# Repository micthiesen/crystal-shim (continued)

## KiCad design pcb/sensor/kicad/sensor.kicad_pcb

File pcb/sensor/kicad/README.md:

# Sensor routing handoff

Open [sensor.kicad_pro](sensor.kicad_pro). The compact sensor is **18 × 64 mm,
four layers**, with 16 footprints and zero unrouted connections. Mount
its mask-covered glass face with thin adhesive film, top 2 mm below the rim.
J1 is six outward-face solder pads; the pigtail exits left when looking at the
electronics. No component lead or mount sits between electrode copper and glass.

The glass-facing B.Cu electrodes and In2.Cu driven shields are fixed geometry.
F.Cu holds electronics and all ordinary routes; In1.Cu provides continuous ground.
The accepted routing has 117 track segments and nine tented vias, including five
GND vias. All ground pads share the F.Cu fill, connected to In1.Cu. Preserve the
routed board and its exact accepted glass-side breakouts. Through vias default to
0.45/0.20 mm.

Strict ERC and schematic parity are clean. Six exact, UUID-bound padstack
warnings are excluded because the intentional driven-shield pads exist only on
In2.Cu. Their complete geometry/net contract is checked separately; unrelated
padstack warnings remain enabled. See the
[routing guide](../../../docs/design/routing-guardrails.md),
[design basis](../../../docs/design/sensor-design-basis.md) and
[handoff lock](../design/handoff.lock.json) for current acceptance and evidence.
[Final preparation](../design/evidence/final-preparation/) records the outward
pad-number/RIM labels and native mask/paste/via verification. The subsequent
[stencil receipt](../design/evidence/stencil-process/acceptance.json) selects the
100 µm process without changing native geometry.
Older two-layer and above-rim instructions are superseded.

Keep this project, its custom rules and local libraries together. Route, refill
with **B**, save and run `sh scripts/check-routing.sh sensor --final` before
fabrication checks/export. Unconnected items are allowed without `--final`.
Physical capacitance and adhesive response remain commissioning measurements.

Owner routing is accepted in the [routing receipt](../../../docs/design/evidence/sensor-routing-acceptance/README.md). Final pre-fabrication review remains deferred until all three boards are reviewed together.

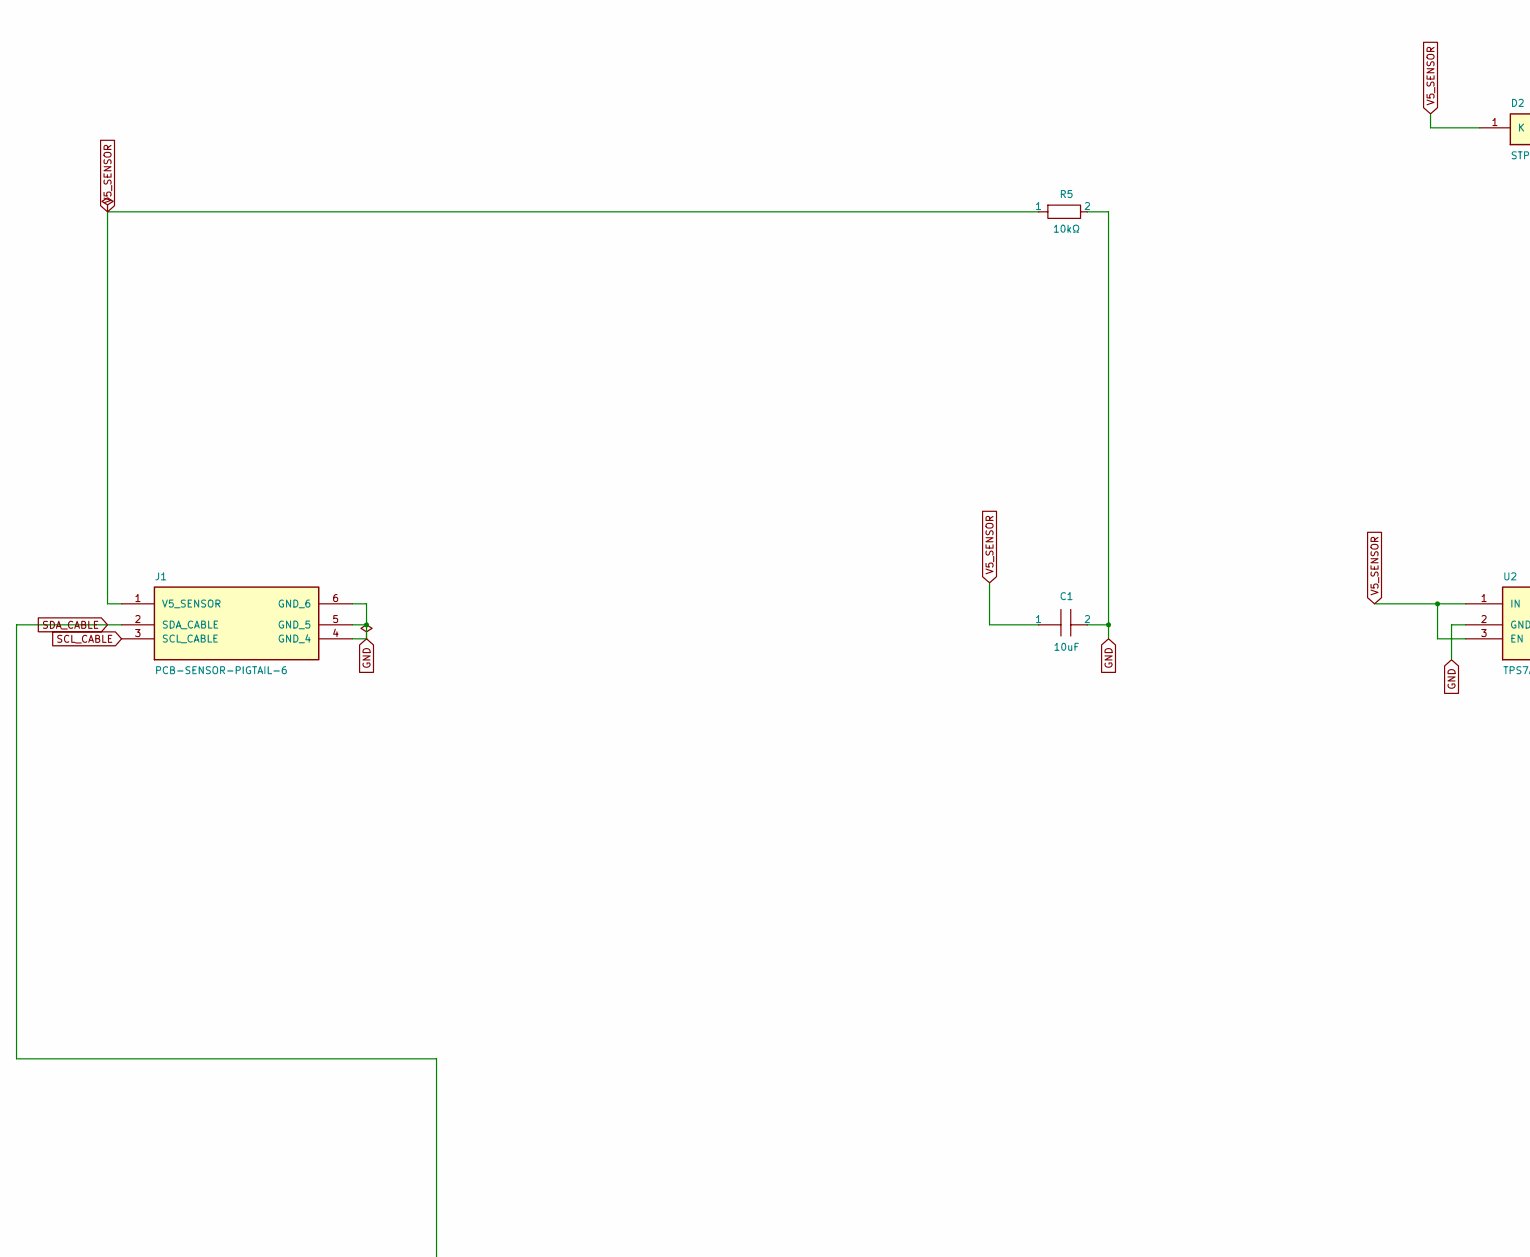
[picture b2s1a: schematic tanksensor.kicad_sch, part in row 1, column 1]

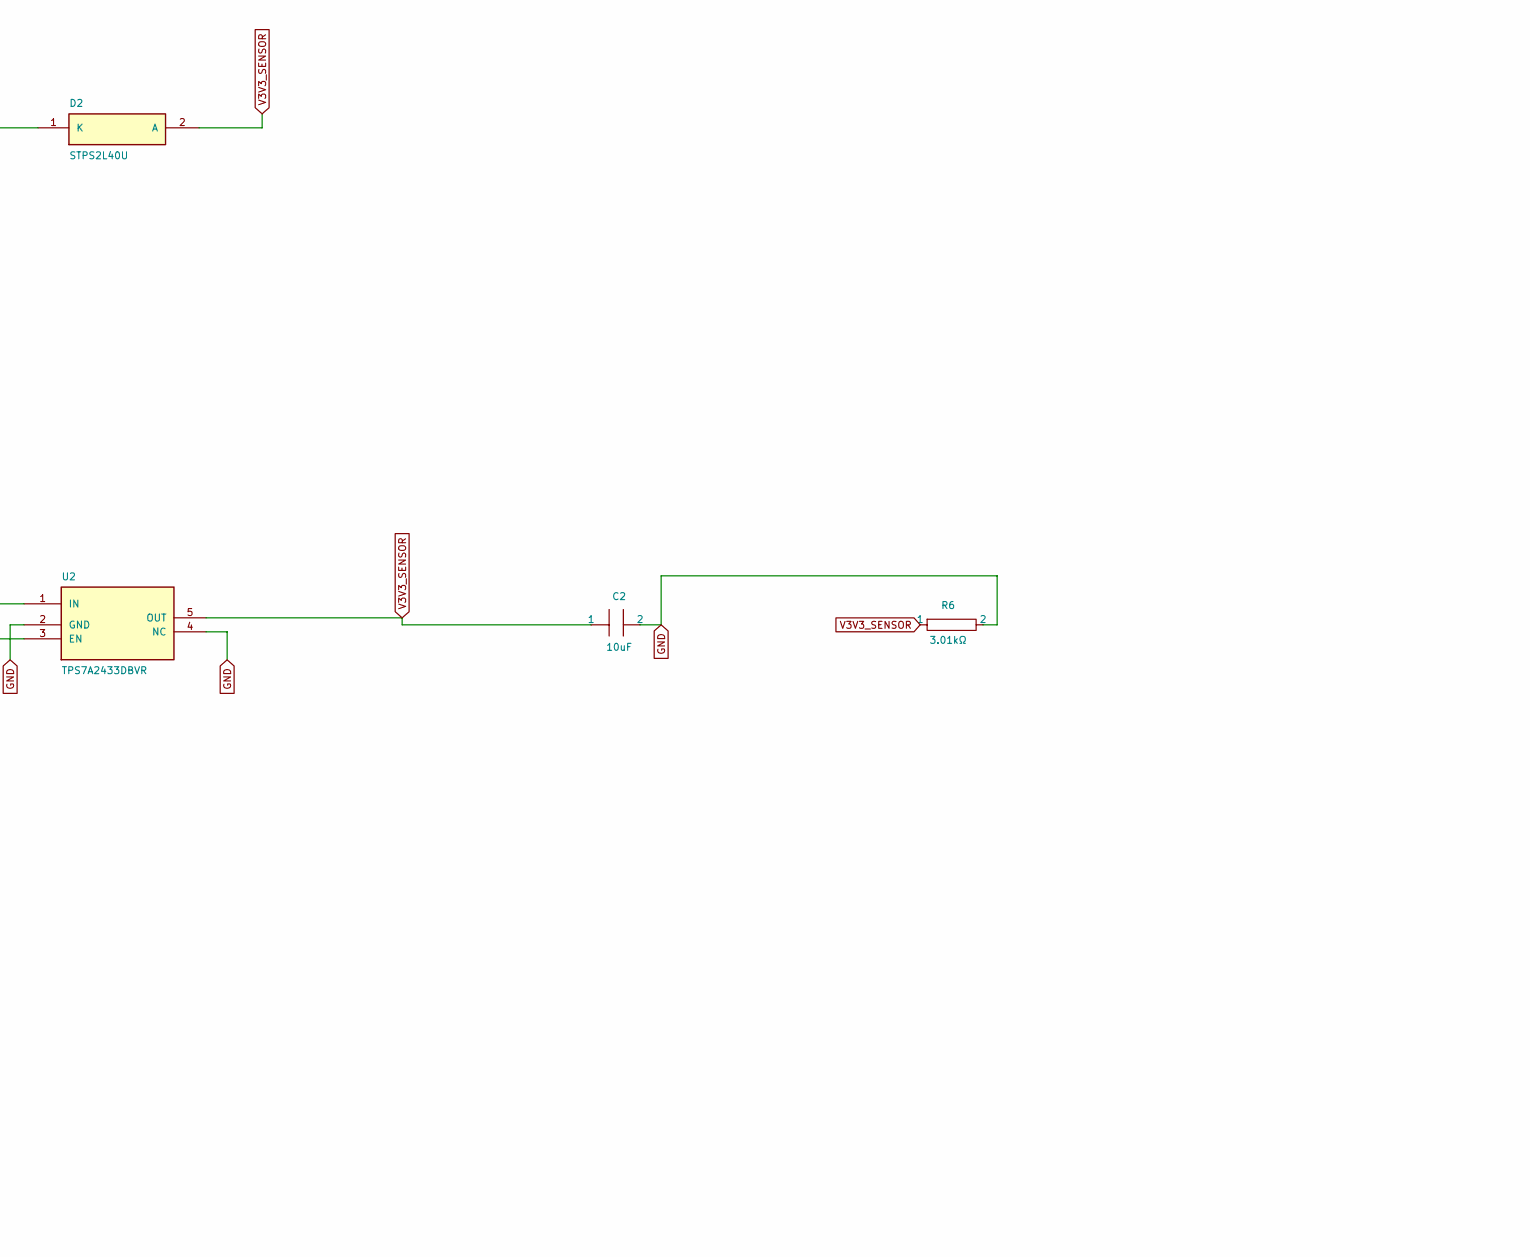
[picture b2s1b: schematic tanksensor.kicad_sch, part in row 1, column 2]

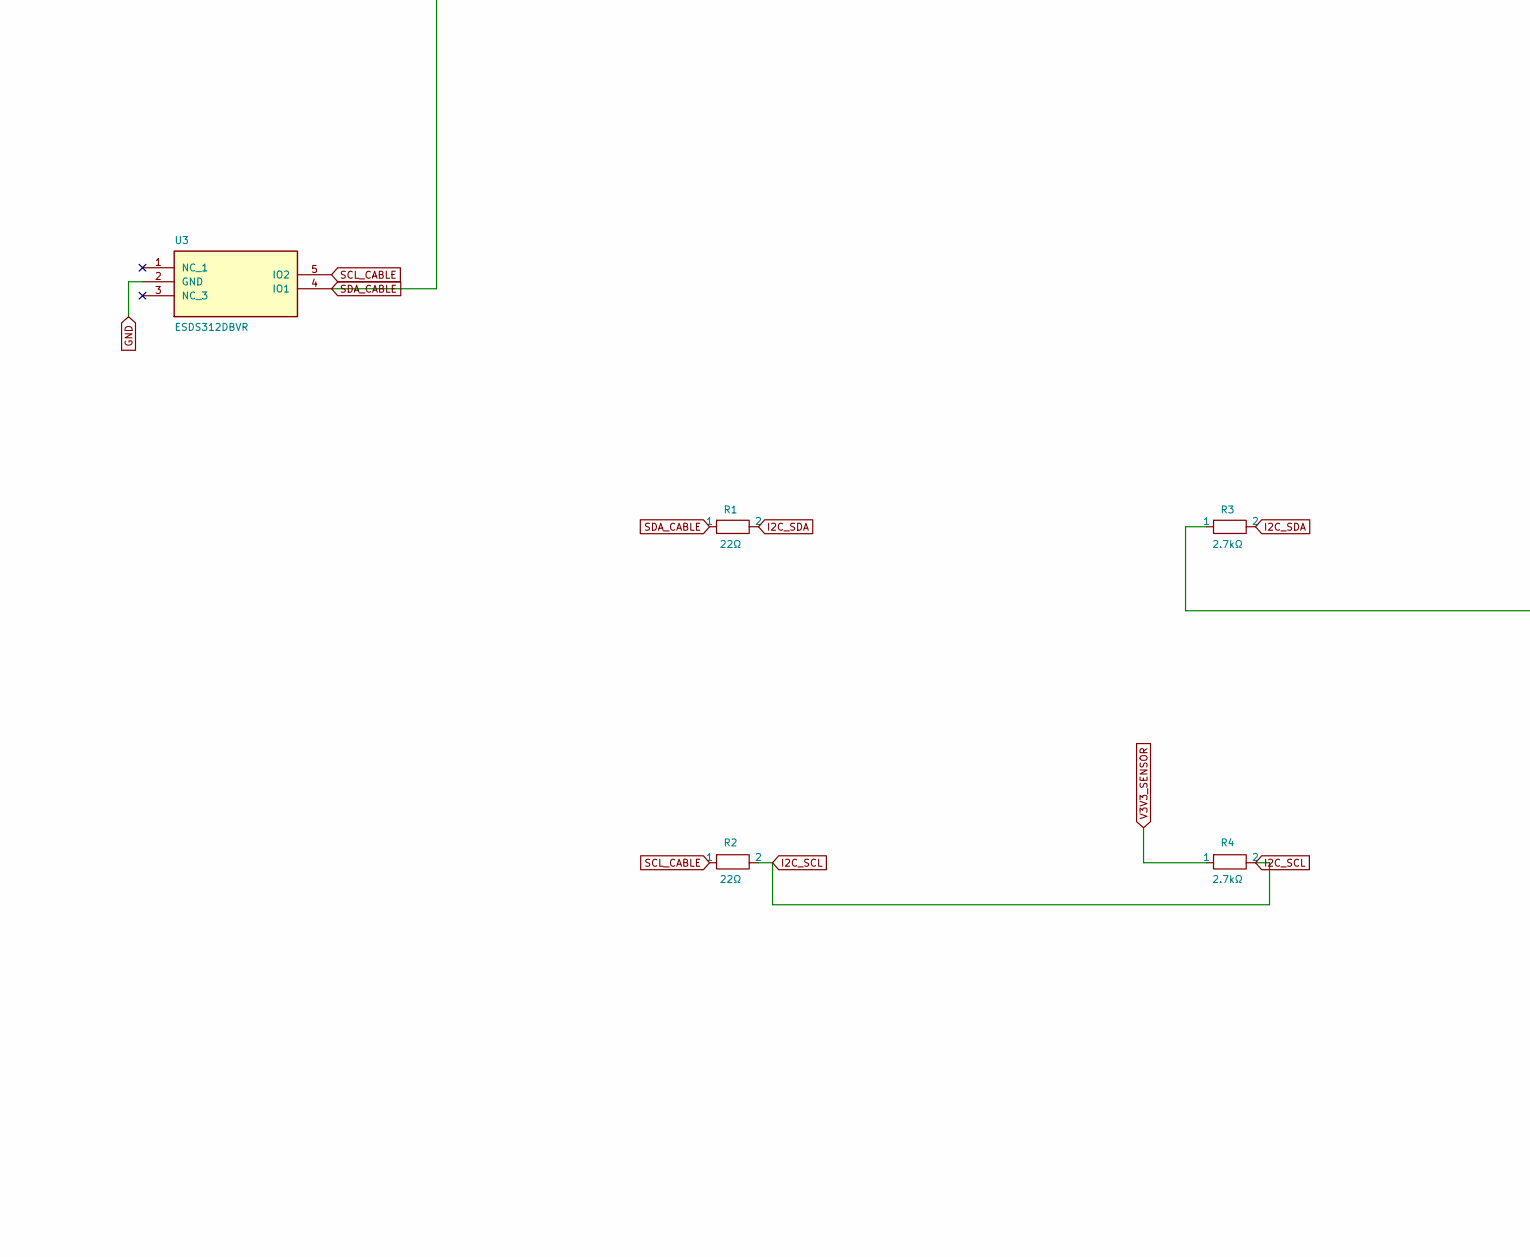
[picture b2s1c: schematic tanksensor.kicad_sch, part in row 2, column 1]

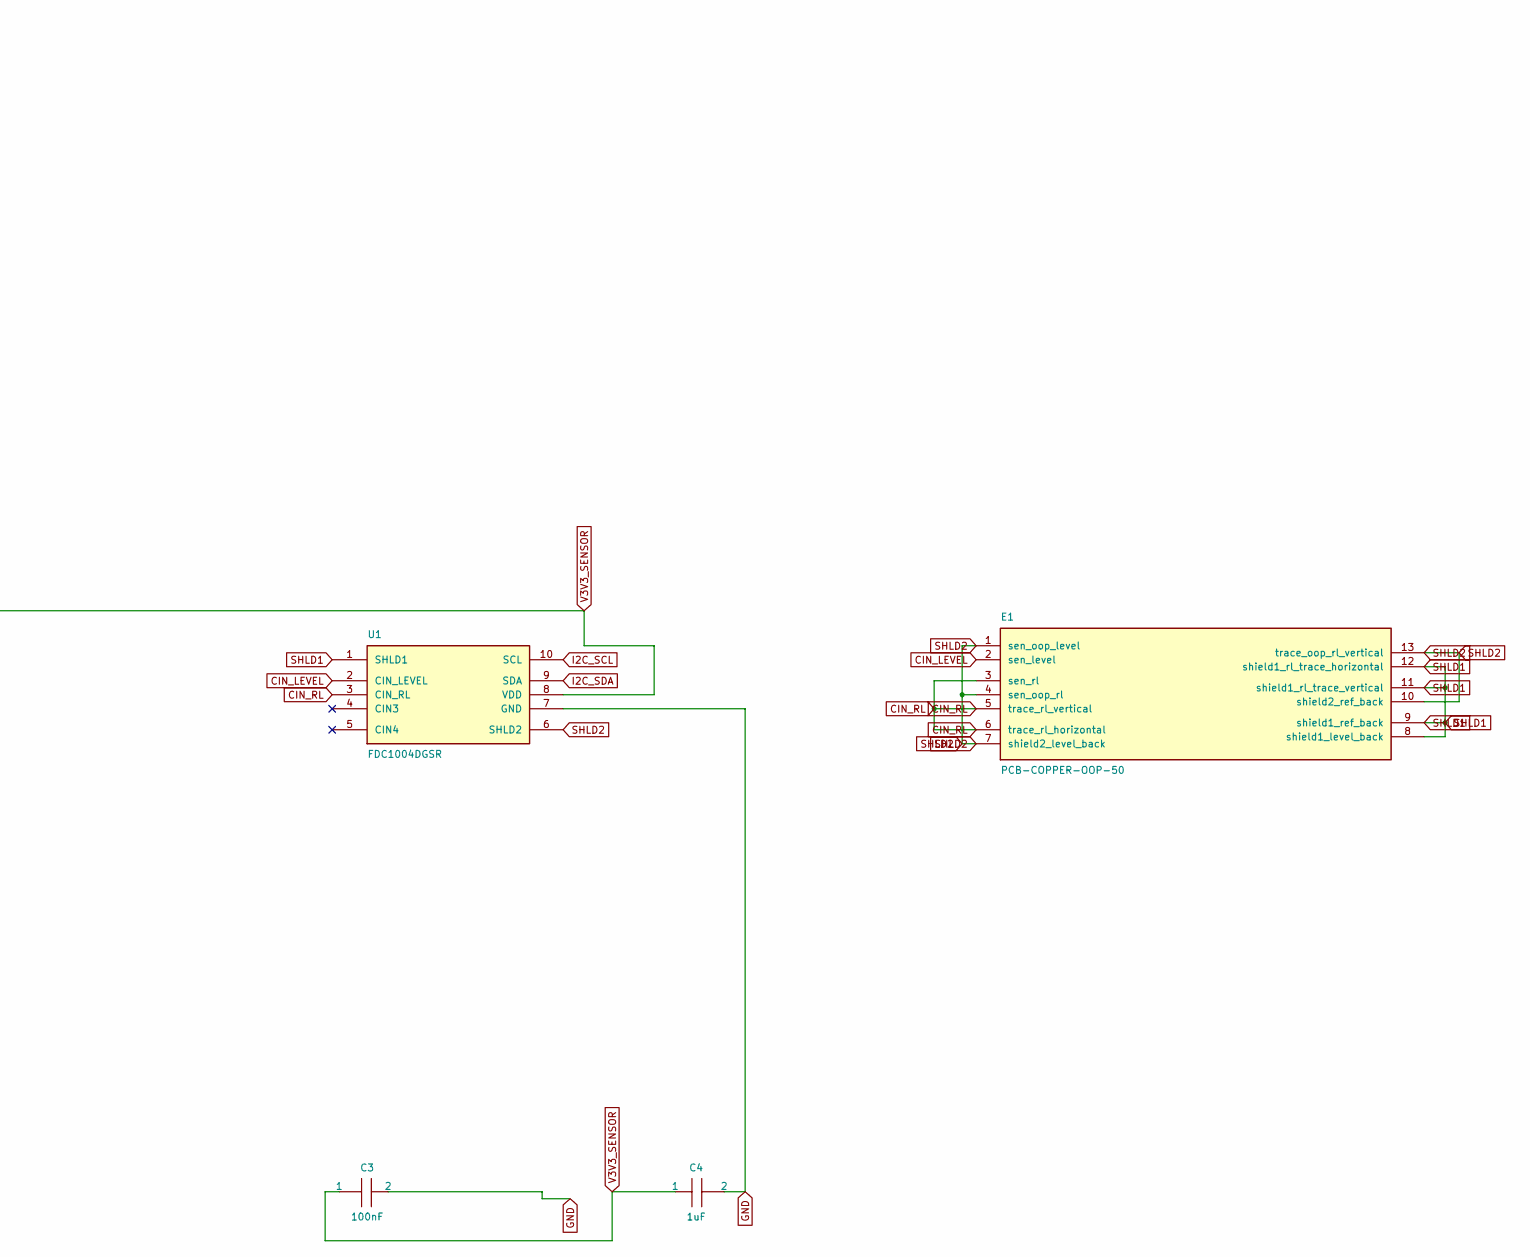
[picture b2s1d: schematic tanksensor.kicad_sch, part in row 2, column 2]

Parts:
C1: 10uF; Sensor_C1; MPN C3216X7R1E106K160AB
C2: 10uF; Sensor_C2; MPN C3216X7R1E106K160AB
C3: 100nF; Sensor_C3; MPN C1608X7R1H104K080AA
C4: 1uF; Sensor_C4; MPN C2012X7R1E105K125AB
D2: STPS2L40U; Sensor_D2; MPN STPS2L40U
E1: PCB-COPPER-OOP-50; Sensor_E1; MPN PCB-COPPER-OOP-50
J1: PCB-SENSOR-PIGTAIL-6; Sensor_J1; MPN PCB-SENSOR-PIGTAIL-6
R1: 22Ω; Sensor_R1; MPN ERJ3EKF22R0V
R2: 22Ω; Sensor_R2; MPN ERJ3EKF22R0V
R3: 2.7kΩ; Sensor_R3; MPN ERJ3EKF2701V
R4: 2.7kΩ; Sensor_R4; MPN ERJ3EKF2701V
R5: 10kΩ; Sensor_R5; MPN ERJ3EKF1002V
R6: 3.01kΩ; Sensor_R6; MPN ERJ3EKF3011V
U1: FDC1004DGSR; Sensor_U1; MPN FDC1004DGSR
U2: TPS7A2433DBVR; Sensor_U2; MPN TPS7A2433DBVR
U3: ESDS312DBVR; Sensor_U3; MPN ESDS312DBVR

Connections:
CIN_LEVEL: E1.2 (sen_level), U1.2 (CIN_LEVEL)
CIN_RL: E1.3 (sen_rl), E1.5 (trace_rl_vertical), E1.6 (trace_rl_horizontal), U1.3 (CIN_RL)
GND: C1.2, C2.2, C3.2, C4.2, J1.4 (GND_4), J1.5 (GND_5), J1.6 (GND_6), R5.2, R6.2, U1.7 (GND), U2.2 (GND), U2.4 (NC), U3.2 (GND)
I2C_SCL: R2.2, R4.2, U1.10 (SCL)
I2C_SDA: R1.2, R3.2, U1.9 (SDA)
SCL_CABLE: J1.3 (SCL_CABLE), R2.1, U3.5 (IO2)
SDA_CABLE: J1.2 (SDA_CABLE), R1.1, U3.4 (IO1)
SHLD1: E1.8 (shield1_level_back), E1.9 (shield1_ref_back), E1.11 (shield1_rl_trace_vertical), E1.12 (shield1_rl_trace_horizontal), U1.1 (SHLD1)
SHLD2: E1.1 (sen_oop_level), E1.4 (sen_oop_rl), E1.7 (shield2_level_back), E1.10 (shield2_ref_back), E1.13 (trace_oop_rl_vertical), U1.6 (SHLD2)
V3V3_SENSOR: C2.1, C3.1, C4.1, D2.2 (A), R3.1, R4.1, R6.1, U1.8 (VDD), U2.5 (OUT)
V5_SENSOR: C1.1, D2.1 (K), J1.1 (V5_SENSOR), R5.1, U2.1 (IN), U2.3 (EN)

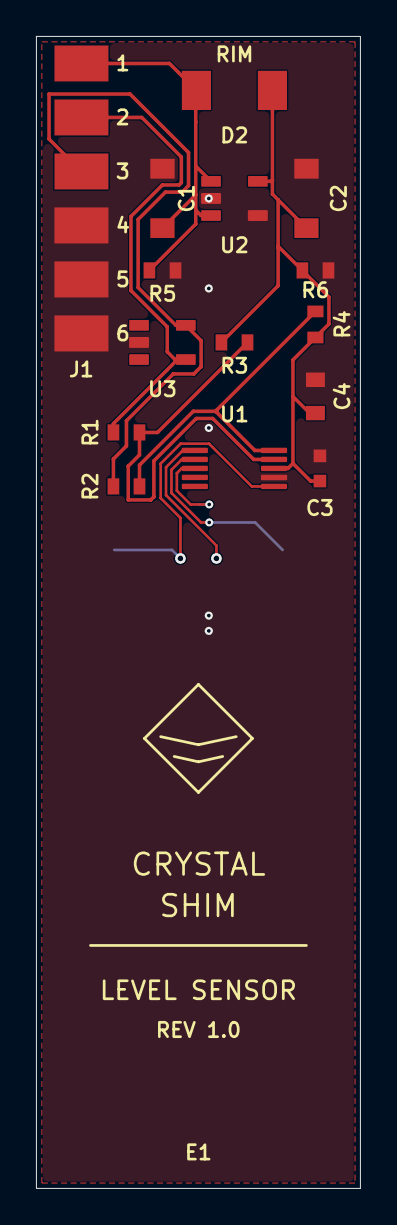
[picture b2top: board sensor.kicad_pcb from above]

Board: 4 copper layers, 18.0 x 64.0 mm, 16 parts (0 on the bottom side), 11 nets.

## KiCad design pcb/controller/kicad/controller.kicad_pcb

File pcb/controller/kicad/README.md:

# Controller routing handoff

Open [controller.kicad_pro](controller.kicad_pro). This is the accepted
150 × 110 mm, four-layer upper board: 117 footprints, **166 unrouted connections**,
clean strict ERC, no schematic parity differences and no ordinary DRC findings.
Four 3.2 mm NPTH mounts are inset 7 mm and align with the mains board below.

The 5 V service input J2 uses JST S2B-XH-A/XHP-2, distinct from the 12 V Micro-Fit ports.
See the [connector ECO](../../../docs/design/evidence/connector-eco/controller/).

Ground pours, reference plane, thermal/ground vias, netclasses, bounded pad
escapes and native custom rules are installed. Follow the
[routing guide](../../../docs/design/routing-guardrails.md) for order and widths.
Keep In1.Cu as ground reference; route USB pairs on F.Cu without vias. The saved
physical stack totals 1.6062 mm; the ordering thickness is nominally 1.6 mm.

[Stacked-layout evidence](evidence/stacked-layout/) records the native move,
source parity, strict ERC, filled DRC and preservation checks. The subsequent
[separator receipt](evidence/dielectric-separator/) changes only the declared
mechanical contract. [Final preparation](evidence/pre-routing-preparation/)
corrects USB shell/duplicate paste, completes service labels and records the
100 µm stencil/order process. [The lock](../design/handoff.lock.json) records acceptance.
Earlier evidence directories describe historical placements.

Keep the project, board, custom rules and local libraries together. Do not export
a new source seed over this native project. Route, refill with **B**, save and run
`sh scripts/check-routing.sh controller --final` before fabrication checks/export.
Unconnected items are allowed when `--final` is omitted during routing.

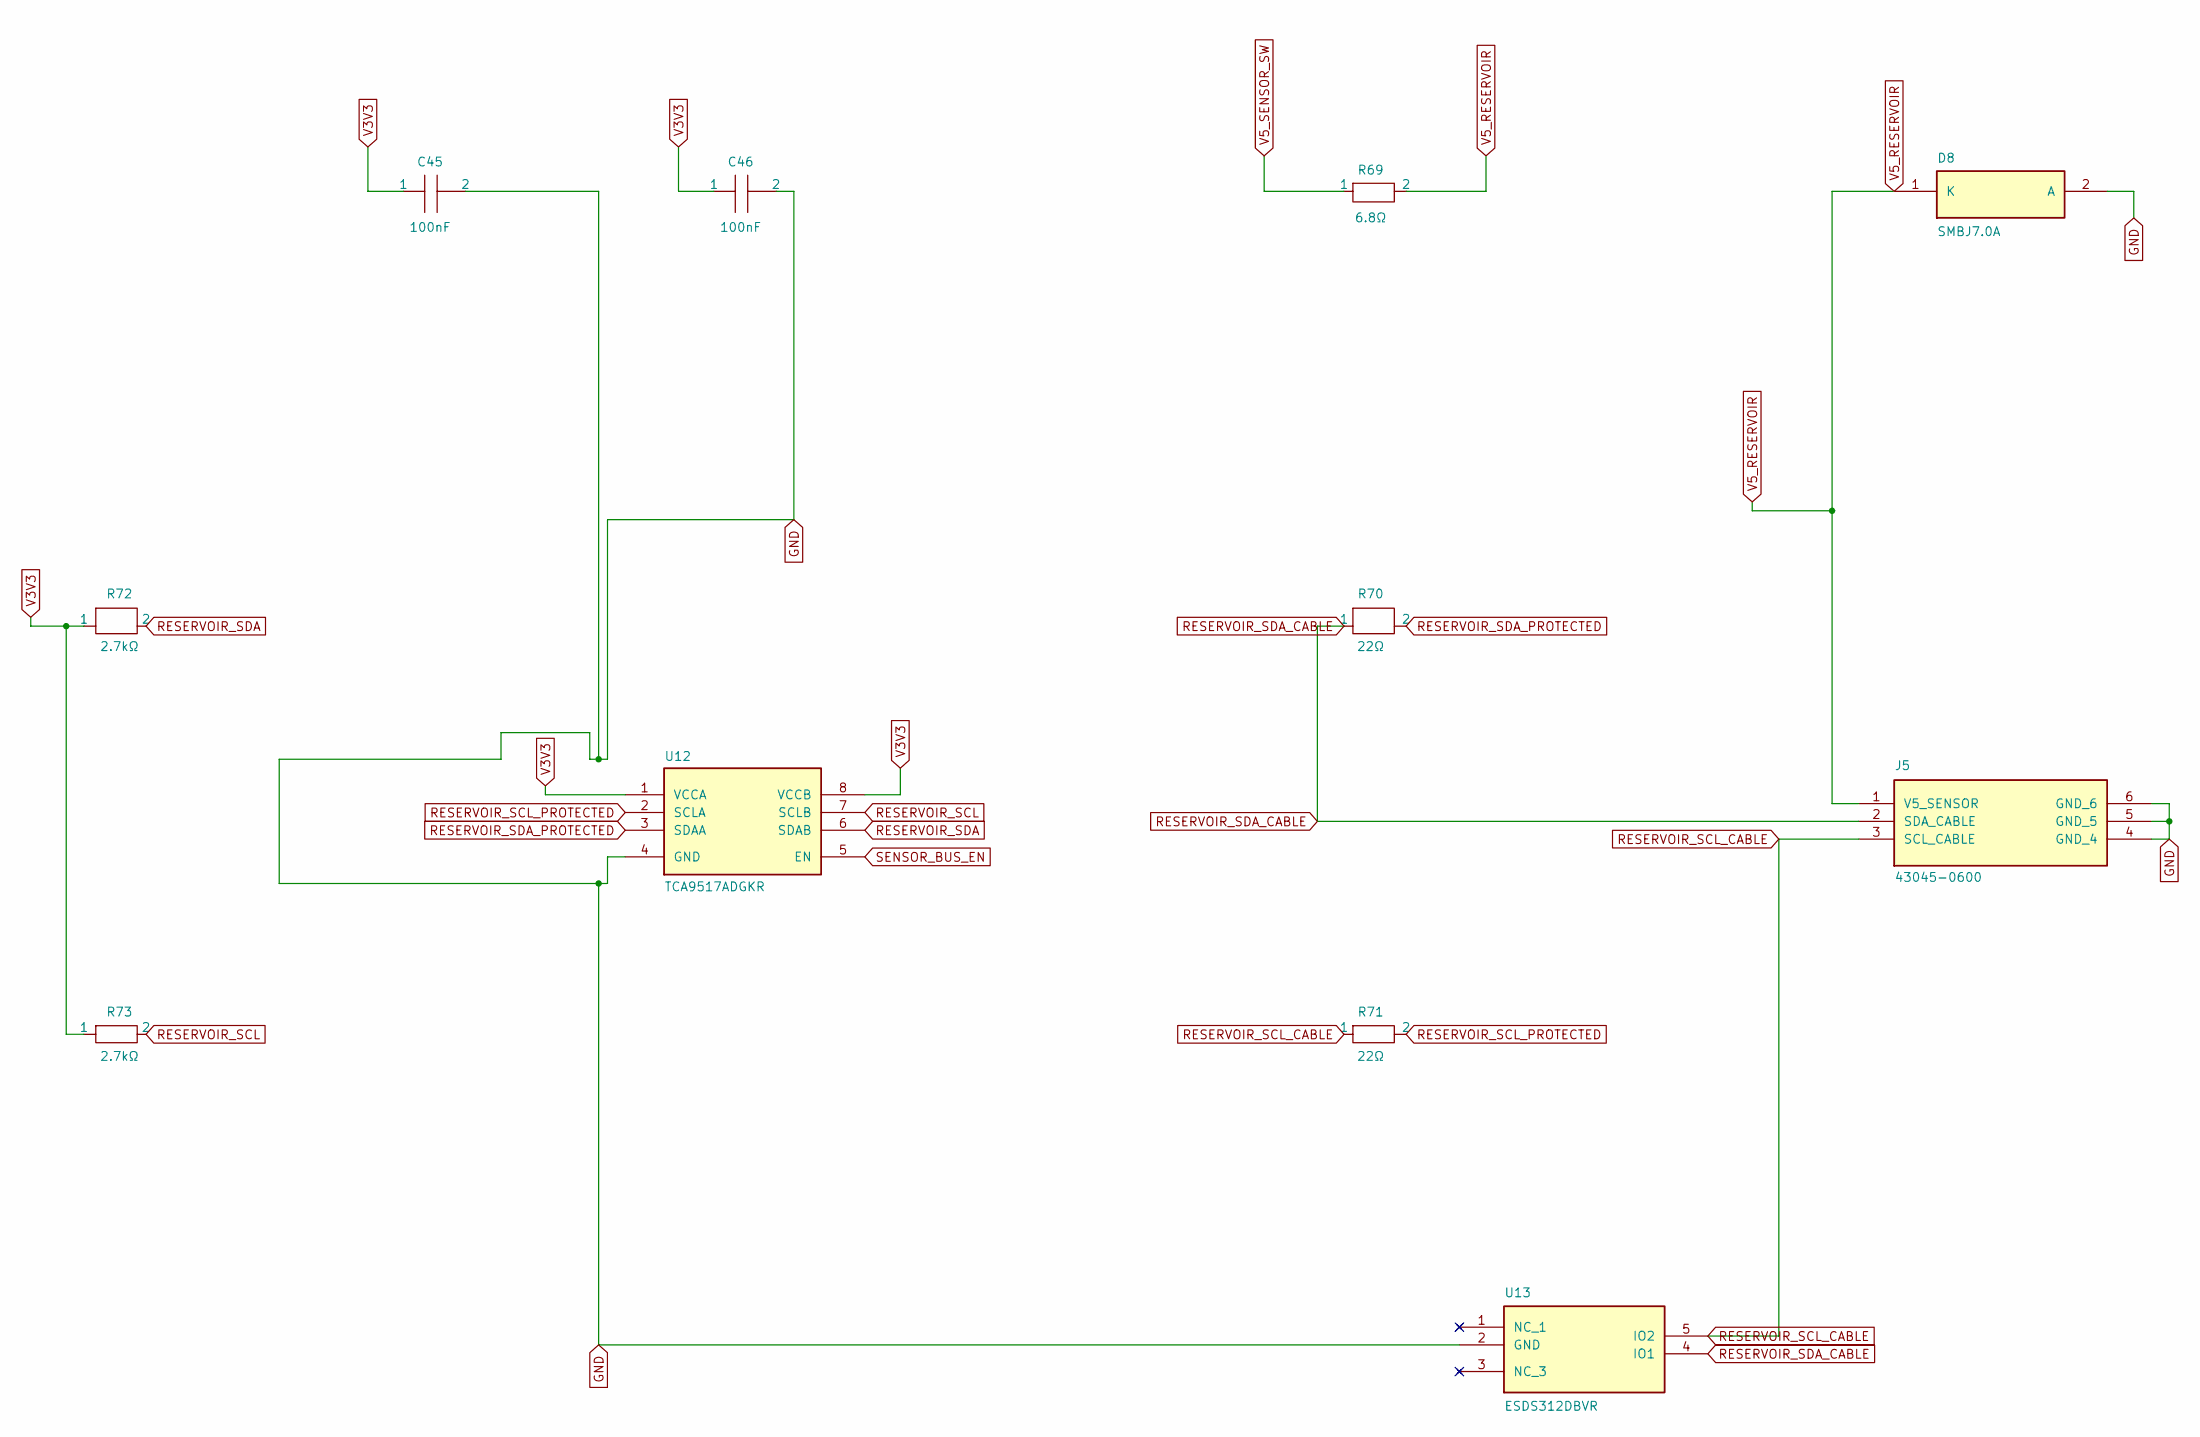
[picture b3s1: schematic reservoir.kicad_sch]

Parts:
C45: 100nF; Controller_C45; MPN C1608X7R1H104K080AA
C46: 100nF; Controller_C46; MPN C1608X7R1H104K080AA
D8: SMBJ7.0A; Controller_D8; MPN SMBJ7.0A
J5: 43045-0600; Controller_J5; MPN 43045-0600
R69: 6.8Ω; Controller_R69; MPN CRCW25126R80FKEGHP
R70: 22Ω; Controller_R70; MPN ERJ3EKF22R0V
R71: 22Ω; Controller_R71; MPN ERJ3EKF22R0V
R72: 2.7kΩ; Controller_R72; MPN ERJ3EKF2701V
R73: 2.7kΩ; Controller_R73; MPN ERJ3EKF2701V
U12: TCA9517ADGKR; Controller_U12; MPN TCA9517ADGKR
U13: ESDS312DBVR; Controller_U13; MPN ESDS312DBVR

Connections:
GND: C45.2, C46.2, D8.2 (A), J5.4 (GND_4), J5.5 (GND_5), J5.6 (GND_6), U12.4 (GND), U13.2 (GND); also elsewhere on the board
RESERVOIR_SCL: R73.2, U12.7 (SCLB); also elsewhere on the board
RESERVOIR_SCL_CABLE: J5.3 (SCL_CABLE), R71.1, U13.5 (IO2)
RESERVOIR_SCL_PROTECTED: R71.2, U12.2 (SCLA)
RESERVOIR_SDA: R72.2, U12.6 (SDAB); also elsewhere on the board
RESERVOIR_SDA_CABLE: J5.2 (SDA_CABLE), R70.1, U13.4 (IO1)
RESERVOIR_SDA_PROTECTED: R70.2, U12.3 (SDAA)
SENSOR_BUS_EN: U12.5 (EN); also elsewhere on the board
V3V3: C45.1, C46.1, R72.1, R73.1, U12.1 (VCCA), U12.8 (VCCB); also elsewhere on the board
V5_RESERVOIR: D8.1 (K), J5.1 (V5_SENSOR), R69.2
V5_SENSOR_SW: R69.1; also elsewhere on the board

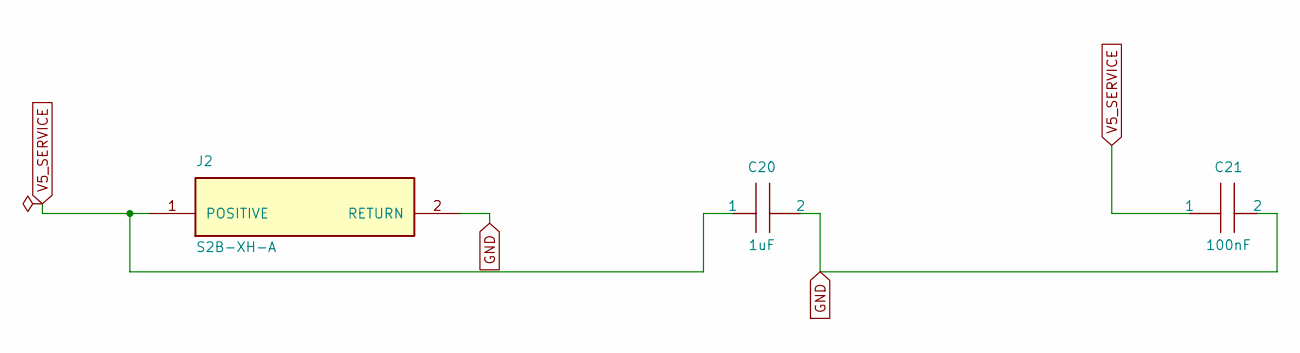
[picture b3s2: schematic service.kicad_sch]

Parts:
C20: 1uF; Controller_C20; MPN C2012X7R1E105K125AB
C21: 100nF; Controller_C21; MPN C1608X7R1H104K080AA
J2: S2B-XH-A; Controller_J2; MPN S2B-XH-A

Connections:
GND: C20.2, C21.2, J2.2 (RETURN); also elsewhere on the board
V5_SERVICE: C20.1, C21.1, J2.1 (POSITIVE); also elsewhere on the board

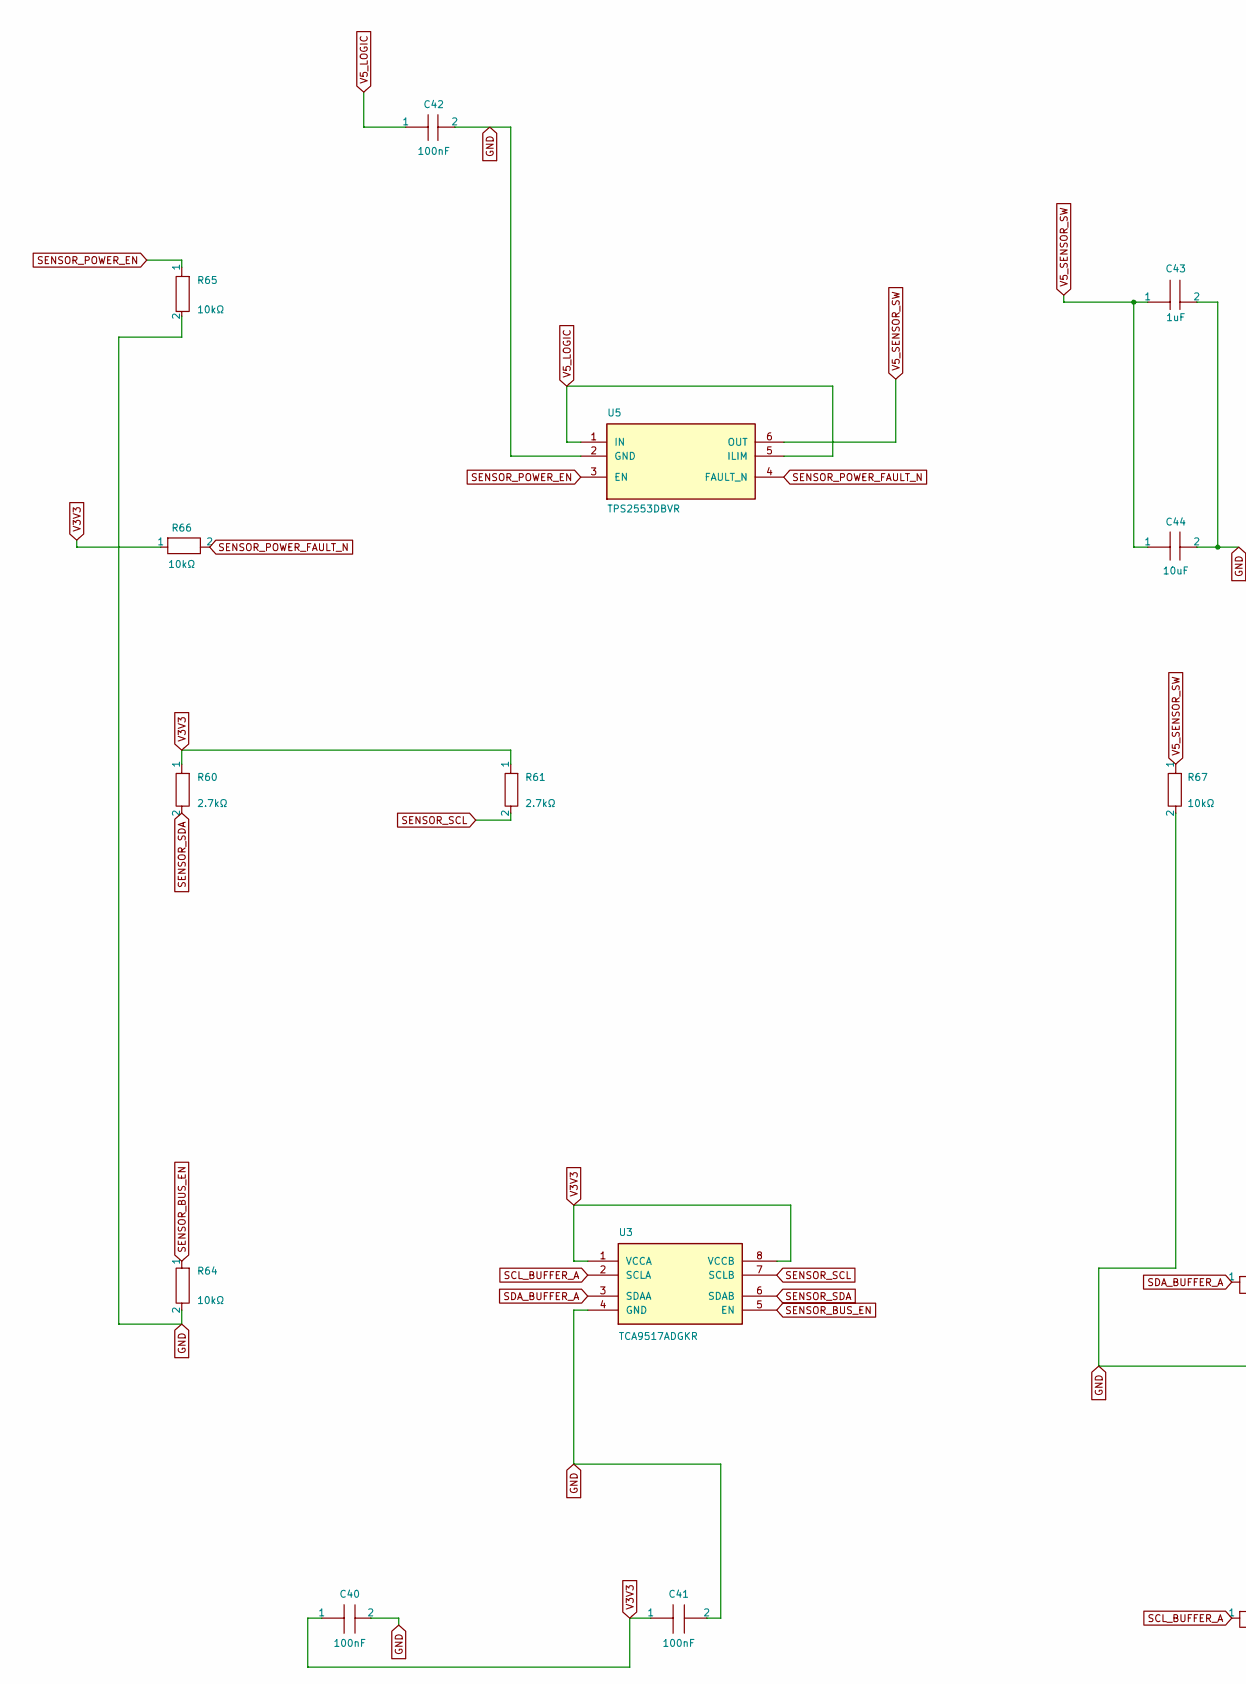
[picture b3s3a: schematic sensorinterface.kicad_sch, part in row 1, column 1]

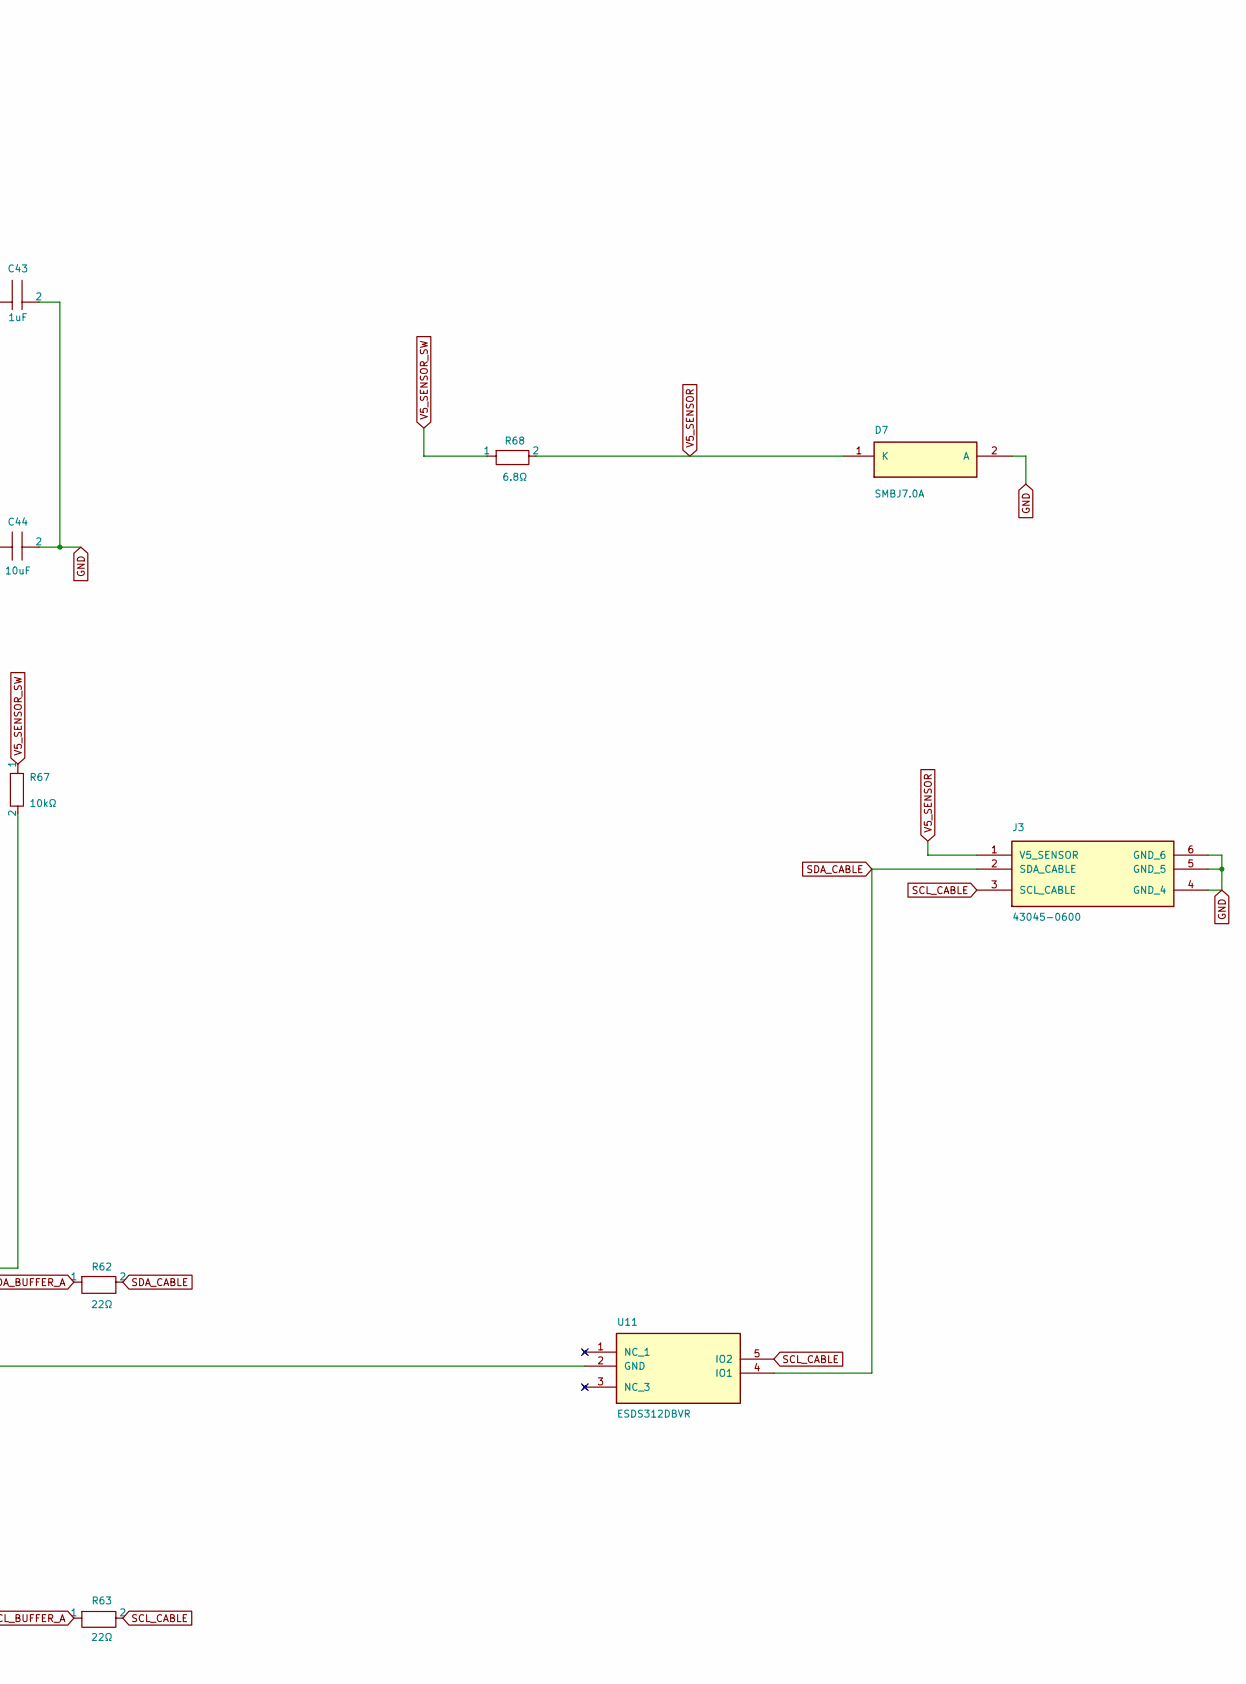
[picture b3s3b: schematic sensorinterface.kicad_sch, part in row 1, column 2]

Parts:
C40: 100nF; Controller_C40; MPN C1608X7R1H104K080AA
C41: 100nF; Controller_C41; MPN C1608X7R1H104K080AA
C42: 100nF; Controller_C42; MPN C1608X7R1H104K080AA
C43: 1uF; Controller_C43; MPN C2012X7R1E105K125AB
C44: 10uF; Controller_C44; MPN C3216X7R1E106K160AB
D7: SMBJ7.0A; Controller_D7; MPN SMBJ7.0A
J3: 43045-0600; Controller_J3; MPN 43045-0600
R60: 2.7kΩ; Controller_R60; MPN ERJ3EKF2701V
R61: 2.7kΩ; Controller_R61; MPN ERJ3EKF2701V
R62: 22Ω; Controller_R62; MPN ERJ3EKF22R0V
R63: 22Ω; Controller_R63; MPN ERJ3EKF22R0V
R64: 10kΩ; Controller_R64; MPN ERJ3EKF1002V
R65: 10kΩ; Controller_R65; MPN ERJ3EKF1002V
R66: 10kΩ; Controller_R66; MPN ERJ3EKF1002V
R67: 10kΩ; Controller_R67; MPN ERJ3EKF1002V
R68: 6.8Ω; Controller_R68; MPN CRCW25126R80FKEGHP
U3: TCA9517ADGKR; Controller_U3; MPN TCA9517ADGKR
U5: TPS2553DBVR; Controller_U5; MPN TPS2553DBVR
U11: ESDS312DBVR; Controller_U11; MPN ESDS312DBVR

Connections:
GND: C40.2, C41.2, C42.2, C43.2, C44.2, D7.2 (A), J3.4 (GND_4), J3.5 (GND_5), J3.6 (GND_6), R64.2, R65.2, R67.2, U3.4 (GND), U5.2 (GND), U11.2 (GND); also elsewhere on the board
SCL_BUFFER_A: R63.1, U3.2 (SCLA)
SCL_CABLE: J3.3 (SCL_CABLE), R63.2, U11.5 (IO2)
SDA_BUFFER_A: R62.1, U3.3 (SDAA)
SDA_CABLE: J3.2 (SDA_CABLE), R62.2, U11.4 (IO1)
SENSOR_BUS_EN: R64.1, U3.5 (EN); also elsewhere on the board
SENSOR_POWER_EN: R65.1, U5.3 (EN); also elsewhere on the board
SENSOR_POWER_FAULT_N: R66.2, U5.4 (FAULT_N); also elsewhere on the board
SENSOR_SCL: R61.2, U3.7 (SCLB); also elsewhere on the board
SENSOR_SDA: R60.2, U3.6 (SDAB); also elsewhere on the board
V3V3: C40.1, C41.1, R60.1, R61.1, R66.1, U3.1 (VCCA), U3.8 (VCCB); also elsewhere on the board
V5_LOGIC: C42.1, U5.1 (IN), U5.5 (ILIM); also elsewhere on the board
V5_SENSOR: D7.1 (K), J3.1 (V5_SENSOR), R68.2
V5_SENSOR_SW: C43.1, C44.1, R67.1, R68.1, U5.6 (OUT); also elsewhere on the board
